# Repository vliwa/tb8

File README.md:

# tb8
## 8bit Transport Buffer Processor
Modified transport triggered architecture using an intermediate buffer in the control unit.  
Allows for 6-bits of internal address space with a 2-bit opcode in a 8-bit instruction.
## Logisim Implementation

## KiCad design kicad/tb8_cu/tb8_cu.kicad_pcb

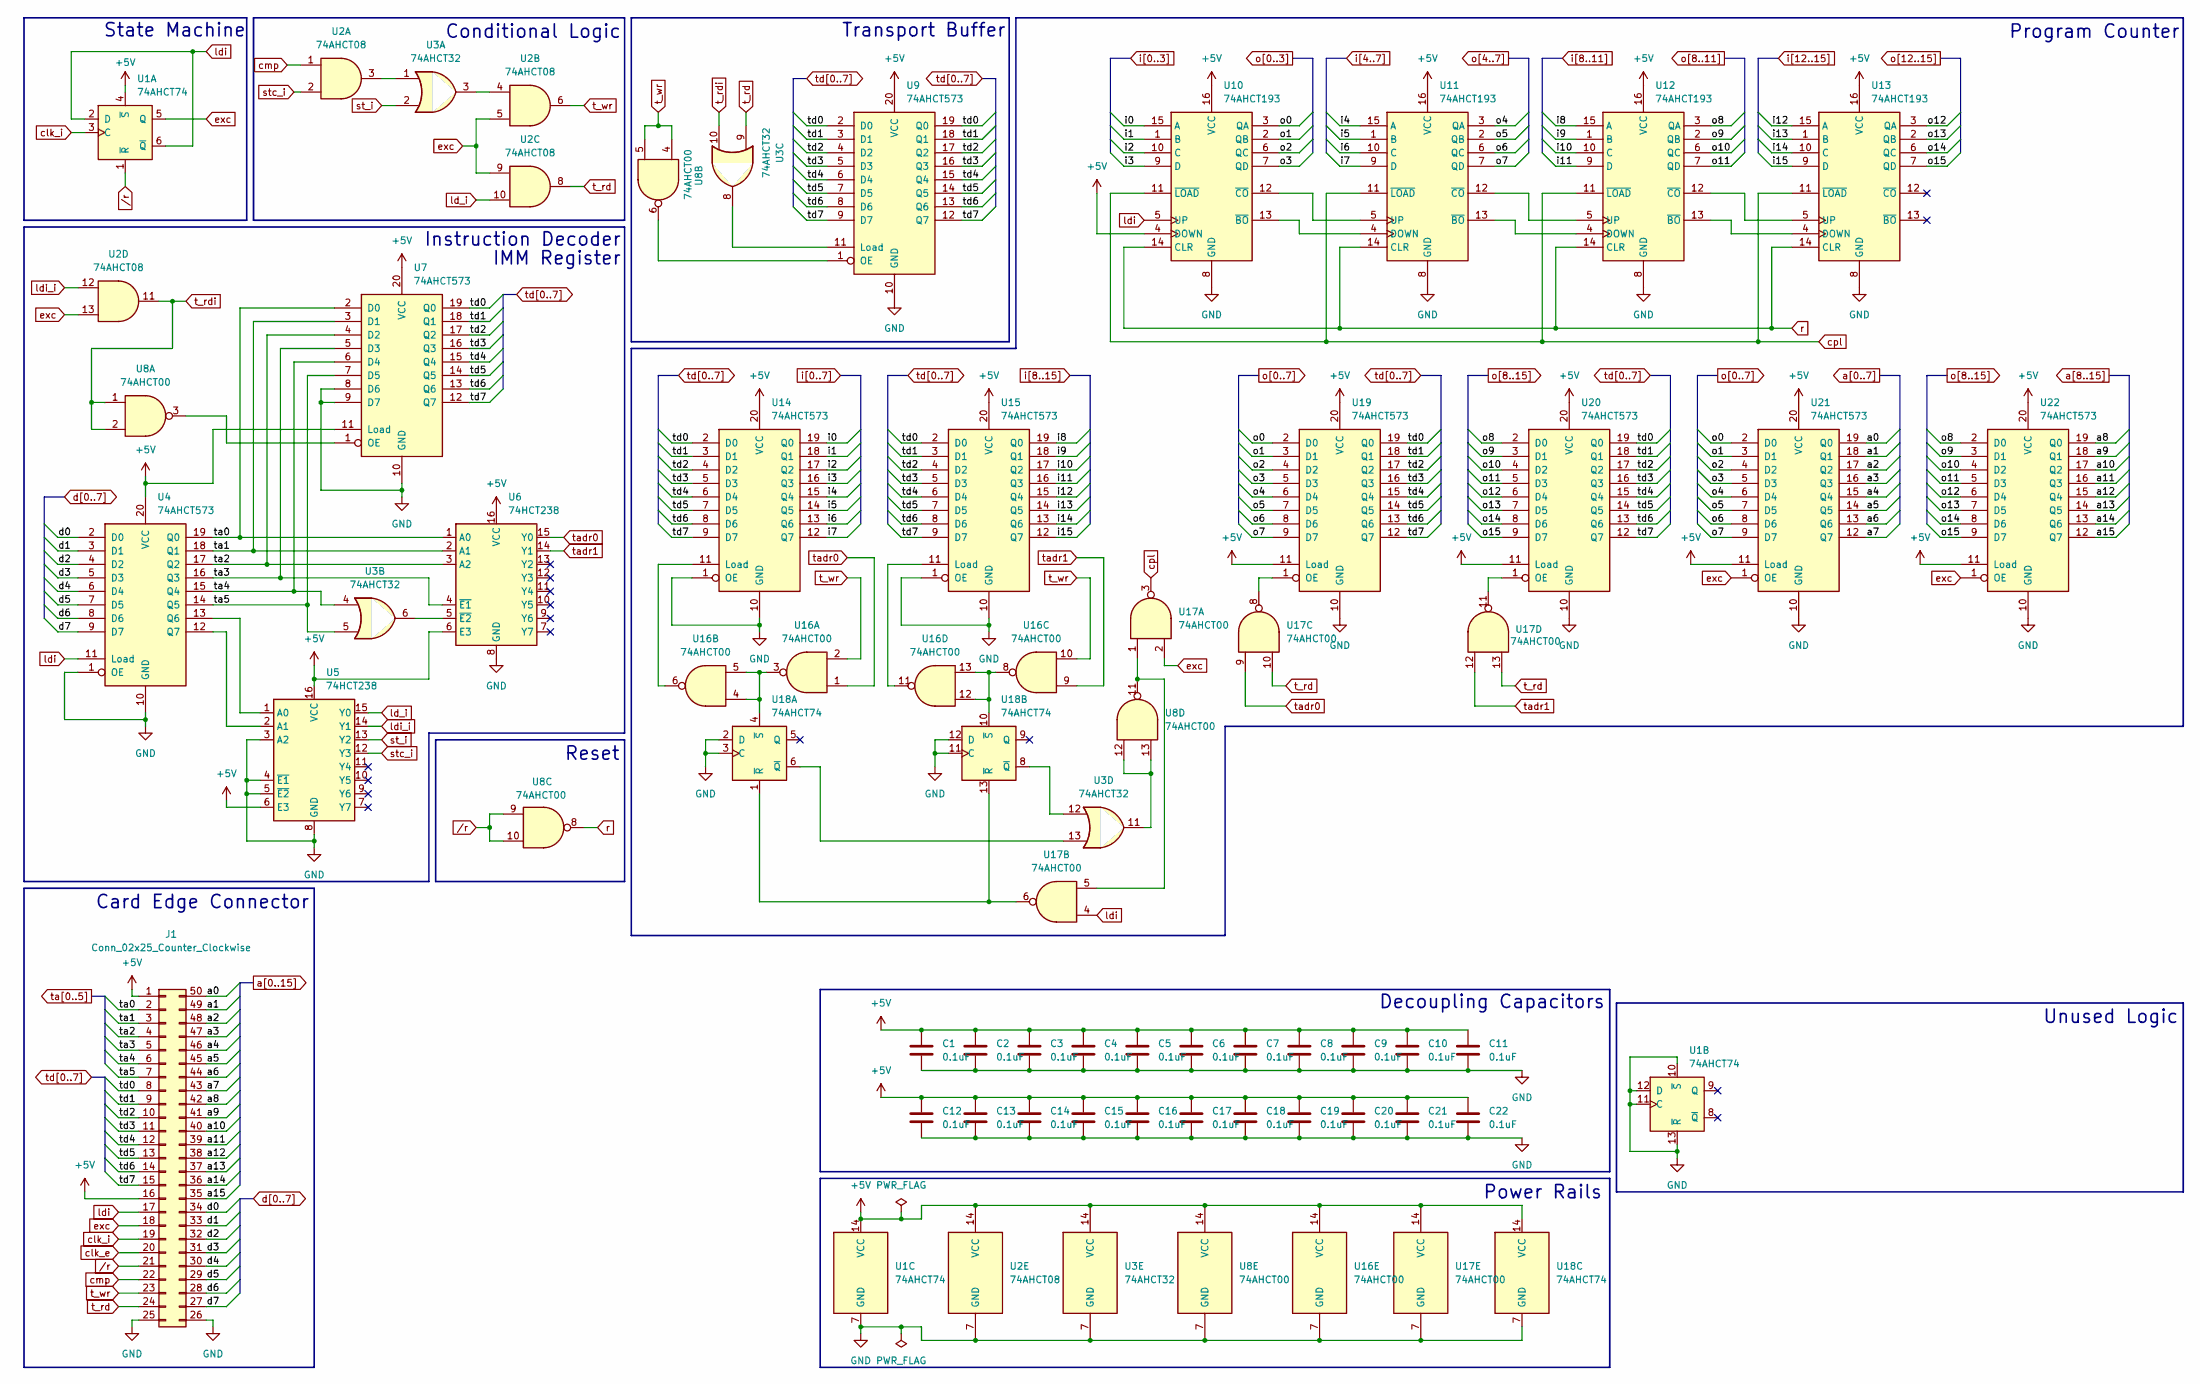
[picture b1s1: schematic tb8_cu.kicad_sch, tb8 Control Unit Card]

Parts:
C1, C2, C3, C4, C5, C6, C7, C8, C9, C10, C11, C12, C13, C14, C15, C16, C17, C18, C19, C20, C21, C22: 0.1uF; C_Rect_L4.0mm_W2.5mm_P2.50mm
J1: Conn_02x25_Counter_Clockwise; 25_2.54spacing
U1, U18: 74AHCT74; DIP-14_W7.62mm_Socket_LongPads
U2: 74AHCT08; DIP-14_W7.62mm_Socket_LongPads
U3: 74AHCT32; DIP-14_W7.62mm_Socket_LongPads
U4, U7, U9, U14, U15, U19, U20, U21, U22: 74AHCT573; DIP-20_W7.62mm_Socket_LongPads
U5, U6: 74HCT238; DIP-16_W7.62mm_Socket_LongPads
U8, U16, U17: 74AHCT00; DIP-14_W7.62mm_Socket_LongPads
U10, U11, U12, U13: 74AHCT193; DIP-16_W7.62mm_Socket_LongPads

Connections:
+5V: C1.1, C2.1, C3.1, C4.1, C5.1, C6.1, C7.1, C8.1, C9.1, C10.1, C11.1, C12.1, C13.1, C14.1, C15.1, C16.1, C17.1, C18.1, C19.1, C20.1, C21.1, C22.1, J1.1, J1.16, U1.4 (~S), U1.14 (VCC), U2.14 (VCC), U3.14 (VCC), U4.20 (VCC), U5.6 (E3), U5.16 (VCC), U6.6 (E3), U6.16 (VCC), U7.11 (Load), U7.20 (VCC), U8.14 (VCC), U9.20 (VCC), U10.4 (DOWN), U10.16 (VCC), U11.16 (VCC), U12.16 (VCC), U13.16 (VCC), U14.20 (VCC), U15.20 (VCC), U16.14 (VCC), U17.14 (VCC), U18.14 (VCC), U19.11 (Load), U19.20 (VCC), U20.11 (Load), U20.20 (VCC), U21.11 (Load), U21.20 (VCC), U22.11 (Load), U22.20 (VCC)
GND: C1.2, C2.2, C3.2, C4.2, C5.2, C6.2, C7.2, C8.2, C9.2, C10.2, C11.2, C12.2, C13.2, C14.2, C15.2, C16.2, C17.2, C18.2, C19.2, C20.2, C21.2, C22.2, J1.25, J1.26, U1.7 (GND), U1.10 (~S), U1.11 (C), U1.12 (D), U1.13 (~R), U2.7 (GND), U3.7 (GND), U4.1 (OE), U4.10 (GND), U5.3 (A2), U5.4 (~E1), U5.5 (~E2), U5.8 (GND), U6.8 (GND), U7.8 (D6), U7.9 (D7), U7.10 (GND), U8.7 (GND), U9.10 (GND), U10.8 (GND), U11.8 (GND), U12.8 (GND), U13.8 (GND), U14.1 (OE), U14.10 (GND), U15.1 (OE), U15.10 (GND), U16.7 (GND), U17.7 (GND), U18.2 (D), U18.3 (C), U18.7 (GND), U18.11 (C), U18.12 (D), U19.10 (GND), U20.10 (GND), U21.10 (GND), U22.10 (GND)
unnamed: U2.3, U3.1
unnamed: U2.4, U3.3
unnamed: U3.11, U8.12, U8.13
unnamed: U4.13 (Q6), U5.1 (A0)
unnamed: U4.12 (Q7), U5.2 (A1)
unnamed: U3.6, U6.5 (~E2)
unnamed: U7.1 (OE), U8.3
unnamed: U3.8, U9.11 (Load)
unnamed: U8.6, U9.1 (OE)
unnamed: U10.13 (~BO), U11.4 (DOWN)
unnamed: U10.12 (~CO), U11.5 (UP)
unnamed: U11.13 (~BO), U12.4 (DOWN)
unnamed: U11.12 (~CO), U12.5 (UP)
unnamed: U12.13 (~BO), U13.4 (DOWN)
unnamed: U12.12 (~CO), U13.5 (UP)
unnamed: U14.11 (Load), U16.6
unnamed: U15.11 (Load), U16.11
unnamed: U8.11, U17.1, U17.5
unnamed: U3.13, U18.6 (~Q)
unnamed: U17.6, U18.1 (~R), U18.13 (~R)
unnamed: U16.3, U16.4, U16.5, U18.4 (~S)
unnamed: U3.12, U18.8 (~Q)
unnamed: U16.8, U16.12, U16.13, U18.10 (~S)
unnamed: U17.8, U19.1 (OE)
unnamed: U17.11, U20.1 (OE)
a0: J1.50, U21.19 (Q0)
a1: J1.49, U21.18 (Q1)
a2: J1.48, U21.17 (Q2)
a3: J1.47, U21.16 (Q3)
a4: J1.46, U21.15 (Q4)
a5: J1.45, U21.14 (Q5)
a6: J1.44, U21.13 (Q6)
a7: J1.43, U21.12 (Q7)
a8: J1.42, U22.19 (Q0)
a9: J1.41, U22.18 (Q1)
a10: J1.40, U22.17 (Q2)
a11: J1.39, U22.16 (Q3)
a12: J1.38, U22.15 (Q4)
a13: J1.37, U22.14 (Q5)
a14: J1.36, U22.13 (Q6)
a15: J1.35, U22.12 (Q7)
clk_e: J1.20
clk_i: J1.19, U1.3 (C)
cmp: J1.22, U2.1
cpl: U10.11 (~LOAD), U11.11 (~LOAD), U12.11 (~LOAD), U13.11 (~LOAD), U17.3
d0: J1.34, U4.2 (D0)
d1: J1.33, U4.3 (D1)
d2: J1.32, U4.4 (D2)
d3: J1.31, U4.5 (D3)
d4: J1.30, U4.6 (D4)
d5: J1.29, U4.7 (D5)
d6: J1.28, U4.8 (D6)
d7: J1.27, U4.9 (D7)
exc: J1.18, U1.5 (Q), U2.5, U2.9, U2.13, U17.2, U21.1 (OE), U22.1 (OE)
i0: U10.15 (A), U14.19 (Q0)
i1: U10.1 (B), U14.18 (Q1)
i2: U10.10 (C), U14.17 (Q2)
i3: U10.9 (D), U14.16 (Q3)
i4: U11.15 (A), U14.15 (Q4)
i5: U11.1 (B), U14.14 (Q5)
i6: U11.10 (C), U14.13 (Q6)
i7: U11.9 (D), U14.12 (Q7)
i8: U12.15 (A), U15.19 (Q0)
i9: U12.1 (B), U15.18 (Q1)
i10: U12.10 (C), U15.17 (Q2)
i11: U12.9 (D), U15.16 (Q3)
i12: U13.15 (A), U15.15 (Q4)
i13: U13.1 (B), U15.14 (Q5)
i14: U13.10 (C), U15.13 (Q6)
i15: U13.9 (D), U15.12 (Q7)
ld_i: U2.10, U5.15 (Y0)
ldi: J1.17, U1.2 (D), U1.6 (~Q), U4.11 (Load), U10.5 (UP), U17.4
ldi_i: U2.12, U5.14 (Y1)
o0: U10.3 (QA), U19.2 (D0), U21.2 (D0)
o1: U10.2 (QB), U19.3 (D1), U21.3 (D1)
o2: U10.6 (QC), U19.4 (D2), U21.4 (D2)
o3: U10.7 (QD), U19.5 (D3), U21.5 (D3)
o4: U11.3 (QA), U19.6 (D4), U21.6 (D4)
o5: U11.2 (QB), U19.7 (D5), U21.7 (D5)
o6: U11.6 (QC), U19.8 (D6), U21.8 (D6)
o7: U11.7 (QD), U19.9 (D7), U21.9 (D7)
o8: U12.3 (QA), U20.2 (D0), U22.2 (D0)
o9: U12.2 (QB), U20.3 (D1), U22.3 (D1)
o10: U12.6 (QC), U20.4 (D2), U22.4 (D2)
o11: U12.7 (QD), U20.5 (D3), U22.5 (D3)
o12: U13.3 (QA), U20.6 (D4), U22.6 (D4)
o13: U13.2 (QB), U20.7 (D5), U22.7 (D5)
o14: U13.6 (QC), U20.8 (D6), U22.8 (D6)
o15: U13.7 (QD), U20.9 (D7), U22.9 (D7)
r: U8.8, U10.14 (CLR), U11.14 (CLR), U12.14 (CLR), U13.14 (CLR)
st_i: U3.2, U5.13 (Y2)
stc_i: U2.2, U5.12 (Y3)
t_rd: J1.24, U2.8, U3.9, U17.10, U17.13
t_rdi: U2.11, U3.10, U8.1, U8.2
t_wr: J1.23, U2.6, U8.4, U8.5, U16.2, U16.10
ta0: J1.2, U4.19 (Q0), U6.1 (A0), U7.2 (D0)
ta1: J1.3, U4.18 (Q1), U6.2 (A1), U7.3 (D1)
ta2: J1.4, U4.17 (Q2), U6.3 (A2), U7.4 (D2)
ta3: J1.5, U4.16 (Q3), U6.4 (~E1), U7.5 (D3)
ta4: J1.6, U3.4, U4.15 (Q4), U7.6 (D4)
ta5: J1.7, U3.5, U4.14 (Q5), U7.7 (D5)
tadr0: U6.15 (Y0), U16.1, U17.9
tadr1: U6.14 (Y1), U16.9, U17.12
td0: J1.8, U7.19 (Q0), U9.2 (D0), U9.19 (Q0), U14.2 (D0), U15.2 (D0), U19.19 (Q0), U20.19 (Q0)
td1: J1.9, U7.18 (Q1), U9.3 (D1), U9.18 (Q1), U14.3 (D1), U15.3 (D1), U19.18 (Q1), U20.18 (Q1)
td2: J1.10, U7.17 (Q2), U9.4 (D2), U9.17 (Q2), U14.4 (D2), U15.4 (D2), U19.17 (Q2), U20.17 (Q2)
td3: J1.11, U7.16 (Q3), U9.5 (D3), U9.16 (Q3), U14.5 (D3), U15.5 (D3), U19.16 (Q3), U20.16 (Q3)
td4: J1.12, U7.15 (Q4), U9.6 (D4), U9.15 (Q4), U14.6 (D4), U15.6 (D4), U19.15 (Q4), U20.15 (Q4)
td5: J1.13, U7.14 (Q5), U9.7 (D5), U9.14 (Q5), U14.7 (D5), U15.7 (D5), U19.14 (Q5), U20.14 (Q5)
td6: J1.14, U7.13 (Q6), U9.8 (D6), U9.13 (Q6), U14.8 (D6), U15.8 (D6), U19.13 (Q6), U20.13 (Q6)
td7: J1.15, U7.12 (Q7), U9.9 (D7), U9.12 (Q7), U14.9 (D7), U15.9 (D7), U19.12 (Q7), U20.12 (Q7)
/r: J1.21, U1.1 (~R), U8.9, U8.10

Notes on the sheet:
Unused Logic
Program Counter
Reset
State Machine
Instruction Decoder
Power Rails
Transport Buffer
Card Edge Connector
Conditional Logic
Decoupling Capacitors
IMM Register

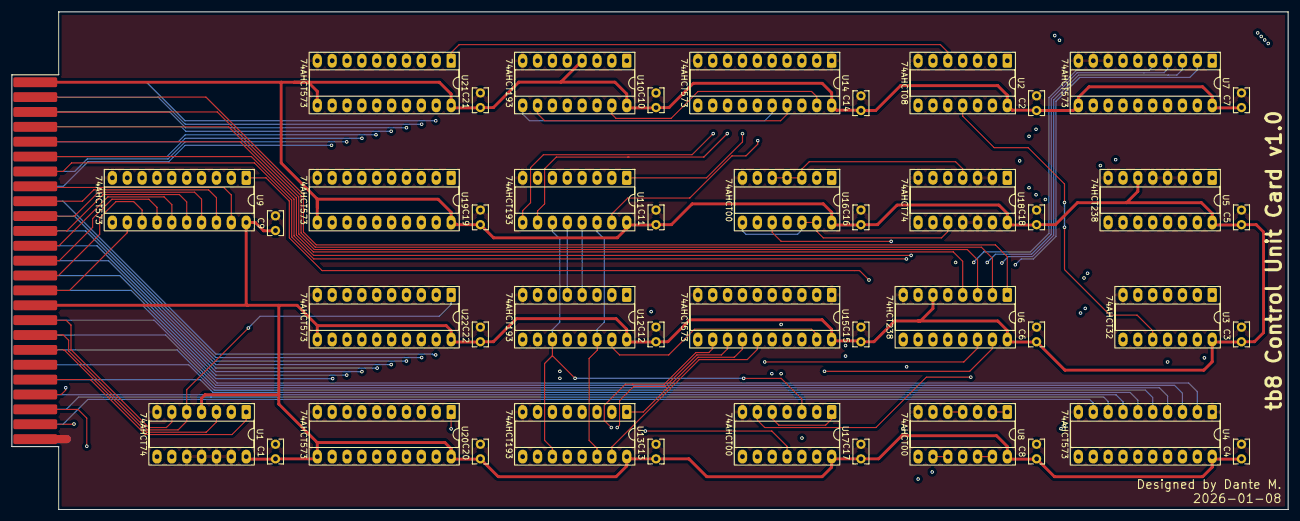
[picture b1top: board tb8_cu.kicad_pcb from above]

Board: 4 copper layers, 218.0 x 85.0 mm, 45 parts (0 on the bottom side), 113 nets.

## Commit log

2025-11-22 74573 are active high LE, modify logisim to match
2025-11-22 split registers file into pages of 8 registers
2025-11-22 test mux for ram caused write issues, removed
2025-11-22 change s-r latches to d flip-flops with set/clear
2025-11-27 readme
2025-11-28 logic changes for TTL hardware
2025-11-28 initial tb8_cu kicad
2025-11-28 tb8_cu sch&pcb in progress
2025-11-29 tb8_cu first revision sch&pcb done
2025-11-29 tba_cu sch pdf
2025-11-29 tb8_cu pcb routing cleanup
2025-11-29 EBC25DCWN footprint
2025-11-29 tb8_cu remove card edge silkscreen
2025-12-05 ALU Control now sets comparator (=,>,<) for stc
2025-12-05 Update outline for comparator changes
2025-12-05 Rename labels ste->stc and eql->cmp
2025-12-05 Use comparator select 11 for bit set comparator
2025-12-05 fix overlapping wire in logisim
2025-12-08 implement carry flag latch for chain alu operations
2025-12-14 checked sch/pcb, pushes to v1.0, generated gerbers
2025-12-14 add name/date to silkscreen, gerber output to zip
2025-12-14 add front panel to logisim
2025-12-14 rearrange logisim
2025-12-16 pushbutton run/stop
2025-12-17 ground unused flipflop inputs
2025-12-17 update sch pdf, update dates
2025-12-17 fix logisim picture
2025-12-17 add front panel jump button
2026-01-09 fix/rotate pcb labels
